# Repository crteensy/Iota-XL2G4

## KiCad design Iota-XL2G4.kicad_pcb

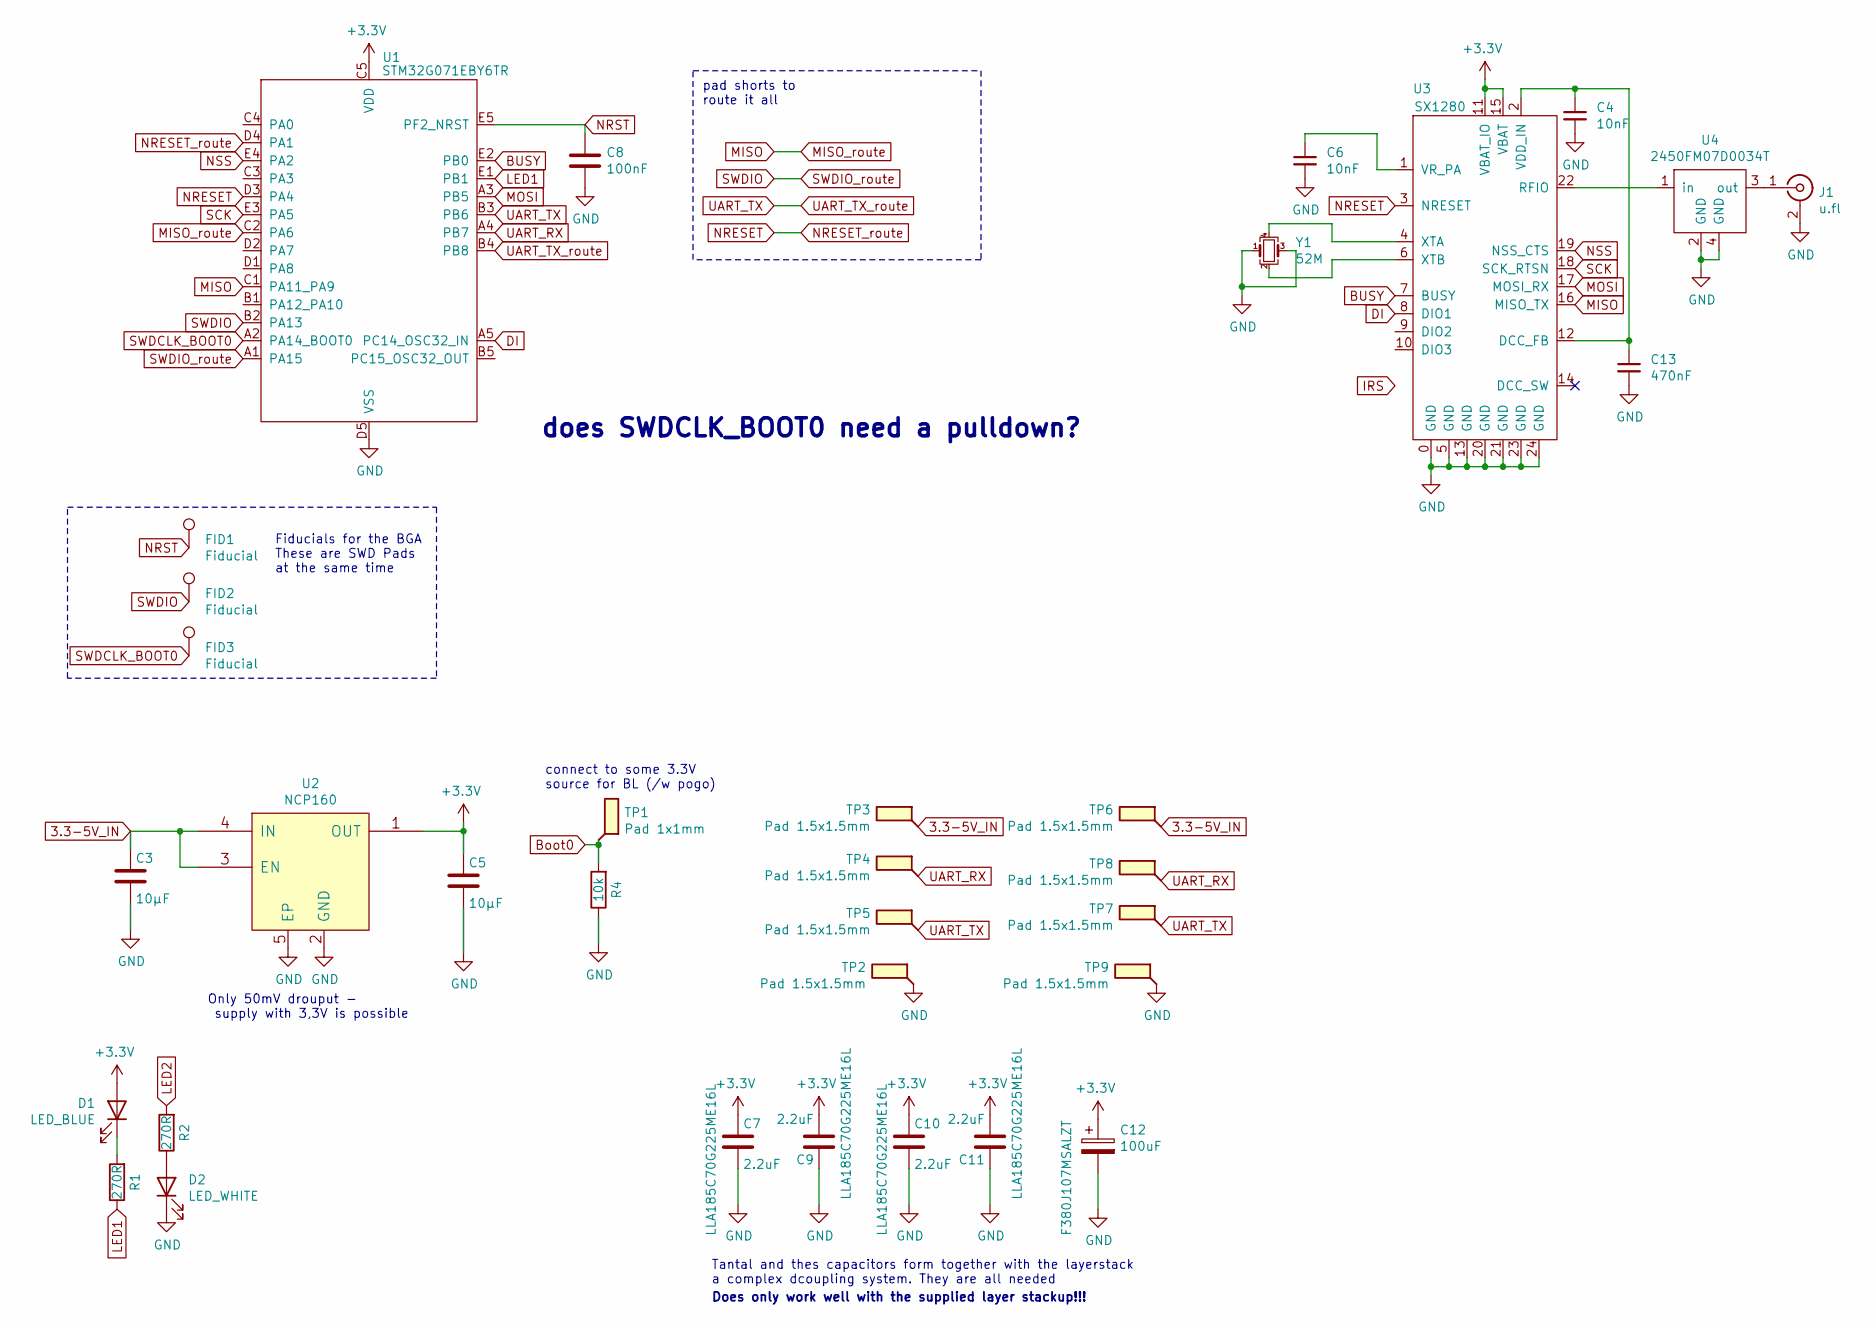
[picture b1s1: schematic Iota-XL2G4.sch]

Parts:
C3, C5: 10µF; L_0402_1005Metric_dense
C4, C6: 10nF; C_0201_0603Metric_dense
C7, C9, C10, C11: 2.2uF; 0805_low_esl_cap_avx_w_via_dense
C8: 100nF; C_0201_0603Metric_dense
C12: 100uF; AVX_S_CASE
C13: 470nF; C_0402_1005Metric_dense
D1: LED_BLUE; LED_0201_0603Metric
D2: LED_WHITE; LED_0201_0603Metric
FID1, FID2, FID3: Fiducial; Fiducial_0.5mm_Dia_1mm_Outer
J1: u.fl; U.FL_Molex_MCRF_73412-0110_Vertical
R1, R2: 270R; R_0201_0603Metric_dense
R4: 10k; R_0201_0603Metric_dense
TP1: Pad 1x1mm; TestPoint_Pad_1.0x1.0mm
TP2, TP3, TP4, TP5: Pad 1.5x1.5mm; TestPoint_Pad_1.5x2mm
TP6, TP7, TP8, TP9: Pad 1.5x1.5mm; corner_castellated
U1: STM32G071EBY6TR; BGA-25_5x5_2.3x2.5mm
U2: NCP160; UDFN-4_1x1mm_P0.65mm
U3: SX1280; QFN-24-1EP_4x4mm_P0.5mm_EP2.6x2.6mm_SX1280_dense
U4: 2450FM07D0034T
Y1: 52M; XTAL_ECS-320-8-47-CKM-TR

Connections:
3.3-5V_IN: C3.1, TP3.1, TP6.1, U2.3 (EN), U2.4 (IN)
+3V3: C5.1, C7.1, C9.2, C10.1, C11.2, C12.1, D1.2 (A), U1.C5 (VDD), U2.1 (OUT), U3.11 (VBAT_IO), U3.15 (VBAT)
BUSY: U1.E2 (PB0), U3.7 (BUSY)
Boot0: R4.2, TP1.1
DI: U1.A5 (PC14_OSC32_IN), U3.8 (DIO1)
GND: C3.2, C4.2, C5.2, C6.2, C7.2, C8.2, C9.1, C10.2, C11.1, C12.2, C13.2, D2.1 (K), J1.2 (Ext), R4.1, TP2.1, TP9.1, U1.D5 (VSS), U2.2 (GND), U2.5 (EP), U3.0 (GND), U3.5 (GND), U3.13 (GND), U3.20 (GND), U3.21 (GND), U3.23 (GND), U3.24 (GND), U4.2 (GND), U4.4 (GND), Y1.1, Y1.3
LED1: R1.1, U1.E1 (PB1)
LED2: R2.2
MISO: U1.C1 (PA11_PA9), U1.C2 (PA6), U3.16 (MISO_TX)
MOSI: U1.A3 (PB5), U3.17 (MOSI_RX)
NRESET: U1.D3 (PA4), U1.D4 (PA1), U3.3 (NRESET)
NRST: C8.1, FID1.1, U1.E5 (PF2_NRST)
NSS: U1.E4 (PA2), U3.19 (NSS_CTS)
unnamed: C6.1, U3.1 (VR_PA)
unnamed: C4.1, C13.1, U3.2 (VDD_IN), U3.12 (DCC_FB)
unnamed: D1.1 (K), R1.2
unnamed: D2.2 (A), R2.1
unnamed: J1.1 (In), U4.3 (out)
unnamed: U3.4 (XTA), Y1.4
unnamed: U3.6 (XTB), Y1.2
unnamed: U3.22 (RFIO), U4.1 (in)
SCK: U1.E3 (PA5), U3.18 (SCK_RTSN)
SWDCLK_BOOT0: FID3.1, U1.A2 (PA14_BOOT0)
SWDIO: FID2.1, U1.A1 (PA15), U1.B2 (PA13)
UART_RX: TP4.1, TP8.1, U1.A4 (PB7)
UART_TX: TP5.1, TP7.1, U1.B3 (PB6), U1.B4 (PB8)

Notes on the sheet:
Only 50mV drouput - supply with 3,3V is possible
connect to some 3.3V source for BL (/w pogo)
Tantal and thes capacitors form together with the layerstack a complex dcoupling system. They are all needed
Fiducials for the BGA These are SWD Pads at the same time
Does only work well with the supplied layer stackup!!!
pad shorts to route it all
does SWDCLK_BOOT0 need a pulldown?

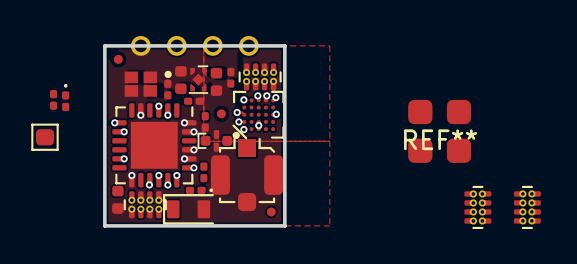
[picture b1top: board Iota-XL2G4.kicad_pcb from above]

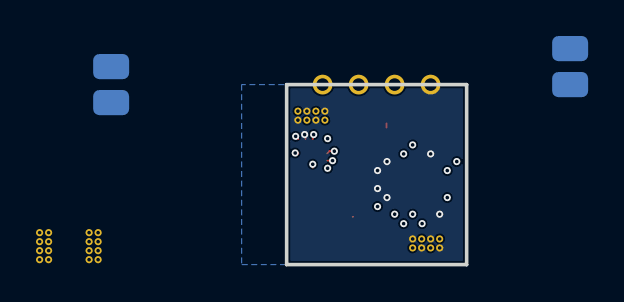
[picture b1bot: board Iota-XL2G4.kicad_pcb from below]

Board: 4 copper layers, 10.0 x 10.0 mm, 34 parts (4 on the bottom side), 25 nets.

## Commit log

2021-03-17 initial layout
2021-03-18 general update
2021-03-18 update schematic
